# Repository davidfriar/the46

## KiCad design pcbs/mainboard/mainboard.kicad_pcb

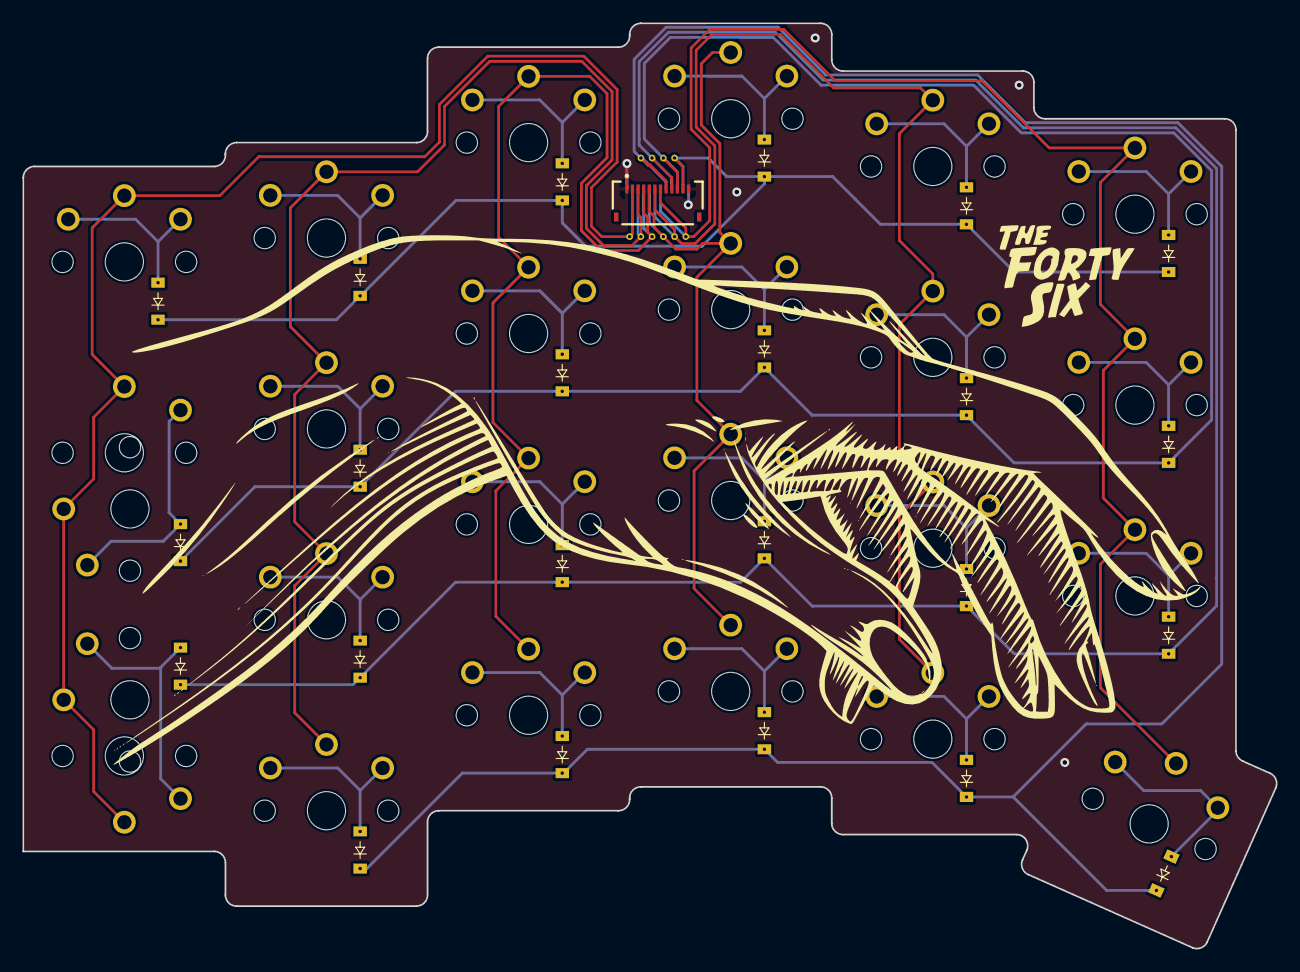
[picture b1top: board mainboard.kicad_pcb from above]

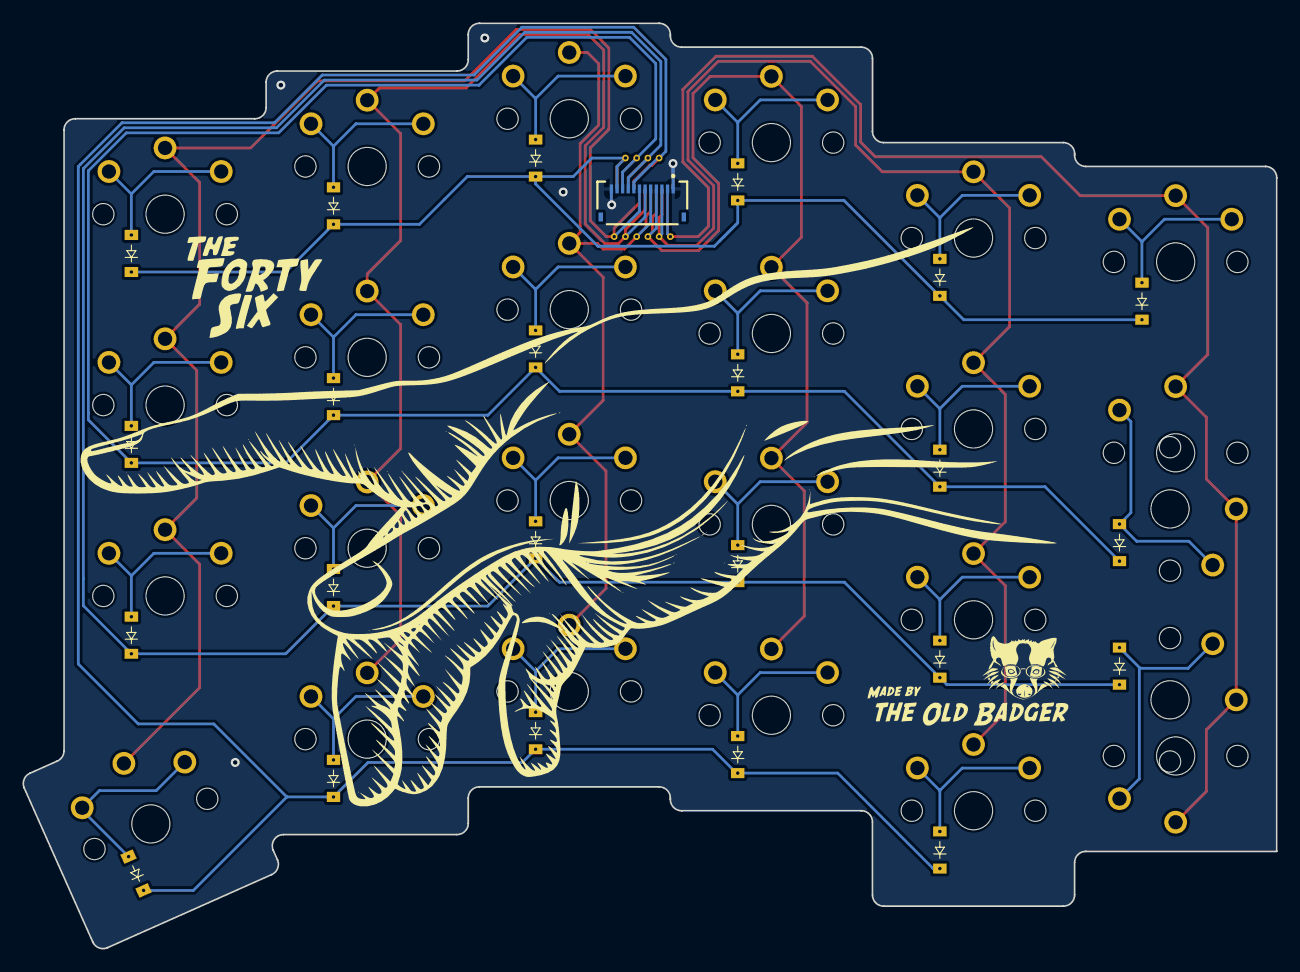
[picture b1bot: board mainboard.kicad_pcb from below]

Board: 2 copper layers, 111.6 x 82.4 mm, 59 parts (3 on the bottom side), 34 nets.

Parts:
D1, D2, D3, D4, D5, D6, D7, D8, D9, D10, D11, D12, D13, D14, D15, D16, D17, D18, D19, D20, D21, D22, D23: diode_tht_sod123
J1: GCT_FFC2B28-12-G
S1, S2, S3, S4, S5, S6, S7, S8, S9, S10, S11, S12, S13, S14, S15, S16, S17, S18, S19, S20, S21, S22, S23, S24, S25: switch_choc_v1_v2
_1, _2, _3, _4, _5, _6, _7, _8, _9, _10: VIA-0.6mm

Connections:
C1: J1.2, S1.2, S22.2, S23.2, S24.2, S25.2, _1.1
C2: J1.3, S2.2, S3.2, S4.2, S5.2, _2.1
C3: J1.4, S6.2, S7.2, S8.2, S9.2, _3.1
C4: J1.5, S10.2, S11.2, S12.2, S13.2, _4.1
C5: J1.6, S14.2, S15.2, S16.2, S17.2, _5.1
C6: J1.7, S18.2, S19.2, S20.2, S21.2, _6.1
GND: J1.1, J1.12
R1: D2.1, D6.1, D10.1, D14.1, D18.1, J1.8, _7.1
R2: D3.1, D7.1, D11.1, D15.1, D19.1, D23.1, J1.9, _8.1
R3: D4.1, D8.1, D12.1, D16.1, D20.1, D22.1, J1.10, _9.1
R4: D1.1, D5.1, D9.1, D13.1, D17.1, D21.1, J1.11, _10.1
index_bottom: D15.2, S15.1
index_middle: D16.2, S16.1
index_thumb: D14.2, S14.1
index_top: D17.2, S17.1
inner_bottom: D19.2, S19.1
inner_middle: D20.2, S20.1
inner_thumb: D18.2, S18.1
inner_top: D21.2, S21.1
middle_bottom: D11.2, S11.1
middle_middle: D12.2, S12.1
middle_thumb: D10.2, S10.1
middle_top: D13.2, S13.1
outer_bottom: D23.2, S22.1, S24.1
outer_middle: D22.2, S23.1, S25.1
outerleft_top: D1.2, S1.1
pinky_bottom: D3.2, S3.1
pinky_middle: D4.2, S4.1
pinky_thumb: D2.2, S2.1
pinky_top: D5.2, S5.1
ring_bottom: D7.2, S7.1
ring_middle: D8.2, S8.1
ring_thumb: D6.2, S6.1
ring_top: D9.2, S9.1

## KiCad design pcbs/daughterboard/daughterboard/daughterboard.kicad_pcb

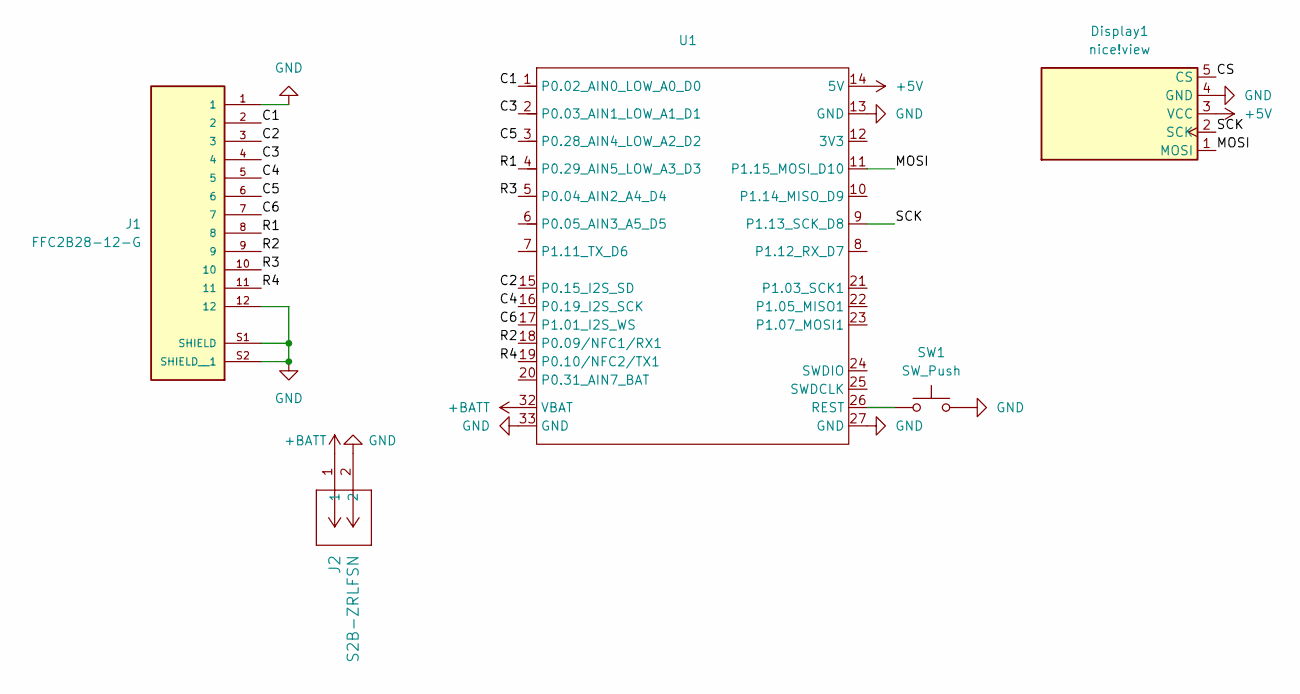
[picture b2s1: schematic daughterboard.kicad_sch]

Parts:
Display1: nice!view; nice_view
J1: FFC2B28-12-G; GCT_FFC2B28-12-G; PARTREV A
J2: S2B-ZRLFSN; CONN_S2B-ZR_JST
SW1: SW_Push; 430471035826
U1: XIAO-nRF52840-Plus-SMD-updated

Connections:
+5V: Display1.3 (VCC), U1.14 (5V)
+BATT: J2.1, U1.32 (VBAT)
/C1: J1.2, U1.1 (P0.02_AIN0_LOW_A0_D0)
/C2: J1.3, U1.15 (P0.15_I2S_SD)
/C3: J1.4, U1.2 (P0.03_AIN1_LOW_A1_D1)
/C4: J1.5, U1.16 (P0.19_I2S_SCK)
/C5: J1.6, U1.3 (P0.28_AIN4_LOW_A2_D2)
/C6: J1.7, U1.17 (P1.01_I2S_WS)
/CS: Display1.5 (CS), U1.8 (P1.12_RX_D7)
/MOSI: Display1.1 (MOSI), U1.11 (P1.15_MOSI_D10)
/R1: J1.8, U1.4 (P0.29_AIN5_LOW_A3_D3)
/R2: J1.9, U1.18 (P0.09/NFC1/RX1)
/R3: J1.10, U1.5 (P0.04_AIN2_A4_D4)
/R4: J1.11, U1.19 (P0.10/NFC2/TX1)
/SCK: Display1.2 (SCK), U1.9 (P1.13_SCK_D8)
GND: Display1.4 (GND), J1.1, J1.12, J1.S1 (SHIELD), J1.S2 (SHIELD__1), J2.2, SW1.2, U1.13 (GND), U1.27 (GND), U1.33 (GND)
unnamed: SW1.1, U1.26 (REST)

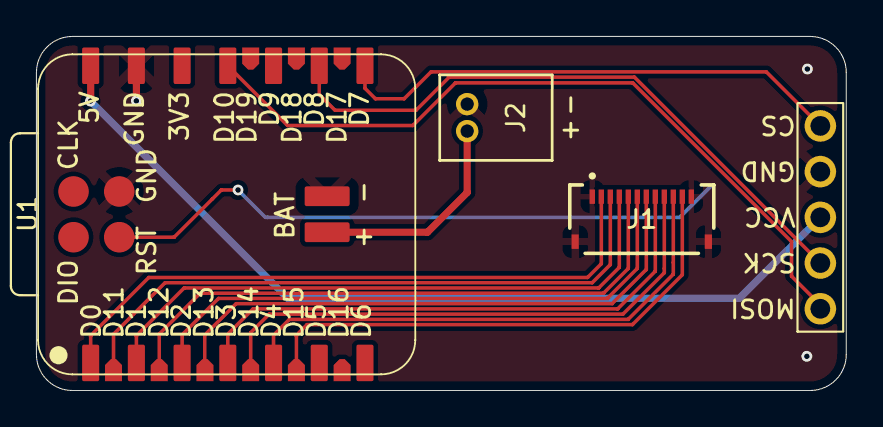
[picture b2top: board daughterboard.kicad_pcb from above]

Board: 2 copper layers, 45.0 x 19.7 mm, 5 parts (1 on the bottom side), 17 nets.

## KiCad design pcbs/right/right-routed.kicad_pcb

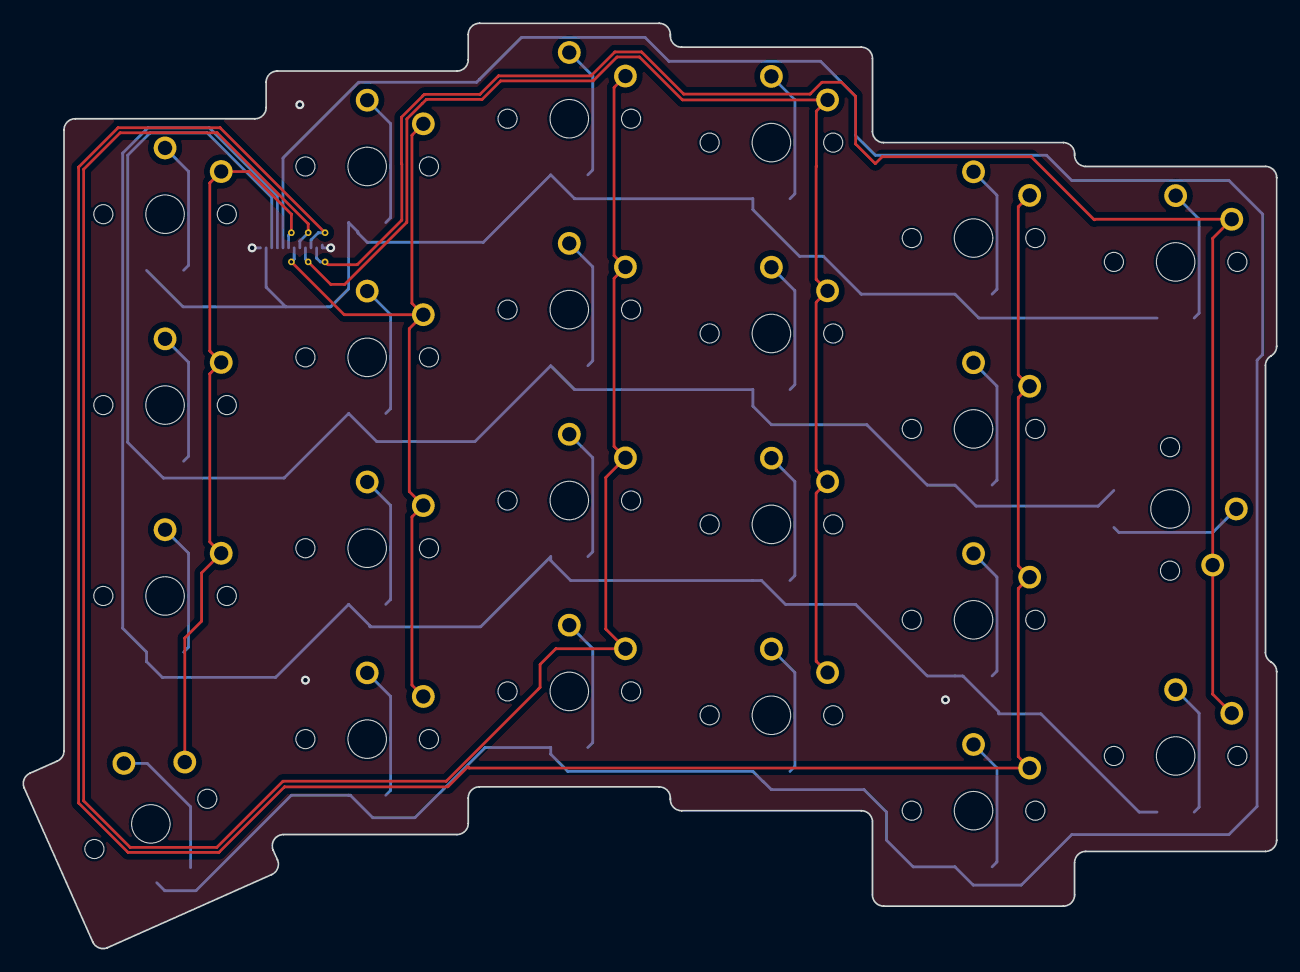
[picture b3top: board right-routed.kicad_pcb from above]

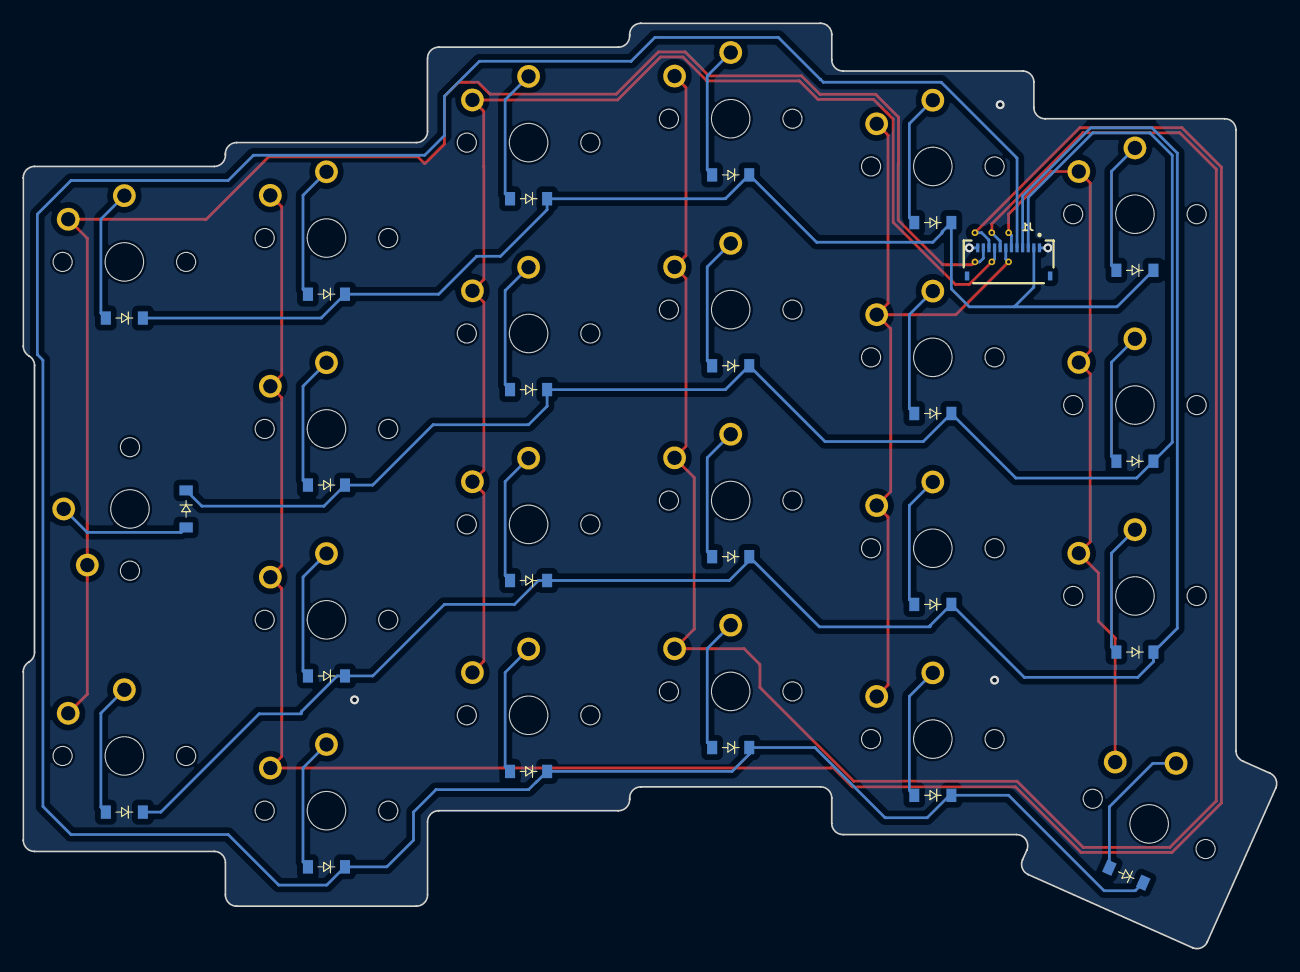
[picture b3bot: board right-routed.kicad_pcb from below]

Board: 2 copper layers, 111.6 x 82.4 mm, 53 parts (24 on the bottom side), 34 nets.

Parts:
D1, D2, D3, D4, D5, D6, D7, D8, D9, D10, D11, D12, D13, D14, D15, D16, D17, D18, D19, D20, D21, D22, D23: ComboDiode
J1: Conn_01x12_Socket; GCT_FFC2B28-12-G
S1, S2, S3, S4, S5, S6, S7, S8, S9, S10, S11, S12, S13, S14, S15, S16, S17, S18, S19, S20, S21, S22, S23: PG1350
_1, _2, _3, _4, _5, _6: VIA-0.6mm

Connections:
C1: J1.6, S20.1, S21.1, S22.1, S23.1, _1.1
C2: J1.7, S16.1, S17.1, S18.1, S19.1, _2.1
C3: J1.8, S12.1, S13.1, S14.1, S15.1, _3.1
C4: J1.9, S8.1, S9.1, S10.1, S11.1, _4.1
C5: J1.10, S4.1, S5.1, S6.1, S7.1, _5.1
C6: J1.11, S1.1, S2.1, S3.1, _6.1
GND: J1.1, J1.12
R1: D4.1, D8.1, D12.1, D16.1, D20.1, J1.5
R2: D1.1, D5.1, D9.1, D13.1, D17.1, D21.1, J1.4
R3: D2.1, D6.1, D10.1, D14.1, D18.1, D22.1, J1.3
R4: D3.1, D7.1, D11.1, D15.1, D19.1, D23.1, J1.2
mirror_index_bottom: D17.2, S17.2
mirror_index_middle: D18.2, S18.2
mirror_index_thumb: D16.2, S16.2
mirror_index_top: D19.2, S19.2
mirror_inner_bottom: D21.2, S21.2
mirror_inner_middle: D22.2, S22.2
mirror_inner_thumb: D20.2, S20.2
mirror_inner_top: D23.2, S23.2
mirror_middle_bottom: D13.2, S13.2
mirror_middle_middle: D14.2, S14.2
mirror_middle_thumb: D12.2, S12.2
mirror_middle_top: D15.2, S15.2
mirror_outerright_bottom: D1.2, S1.2
mirror_outerright_middle: D2.2, S2.2
mirror_outerright_top: D3.2, S3.2
mirror_pinky_bottom: D5.2, S5.2
mirror_pinky_middle: D6.2, S6.2
mirror_pinky_thumb: D4.2, S4.2
mirror_pinky_top: D7.2, S7.2
mirror_ring_bottom: D9.2, S9.2
mirror_ring_middle: D10.2, S10.2
mirror_ring_thumb: D8.2, S8.2
mirror_ring_top: D11.2, S11.2

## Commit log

2025-01-10 fix offset etc
2025-01-11 exclude stl files
2025-03-02 old changes
2025-09-28 committing old changes
2025-10-15 lots of changes
2025-10-15 fixing git problem with deletion
2025-10-19 initial draft of tracking done
2025-10-22 bodge the fillets to make the plate nice
2025-10-22 final tweaks to pcbs before production
2025-12-31 case updates
2026-01-05 case desigh complete
